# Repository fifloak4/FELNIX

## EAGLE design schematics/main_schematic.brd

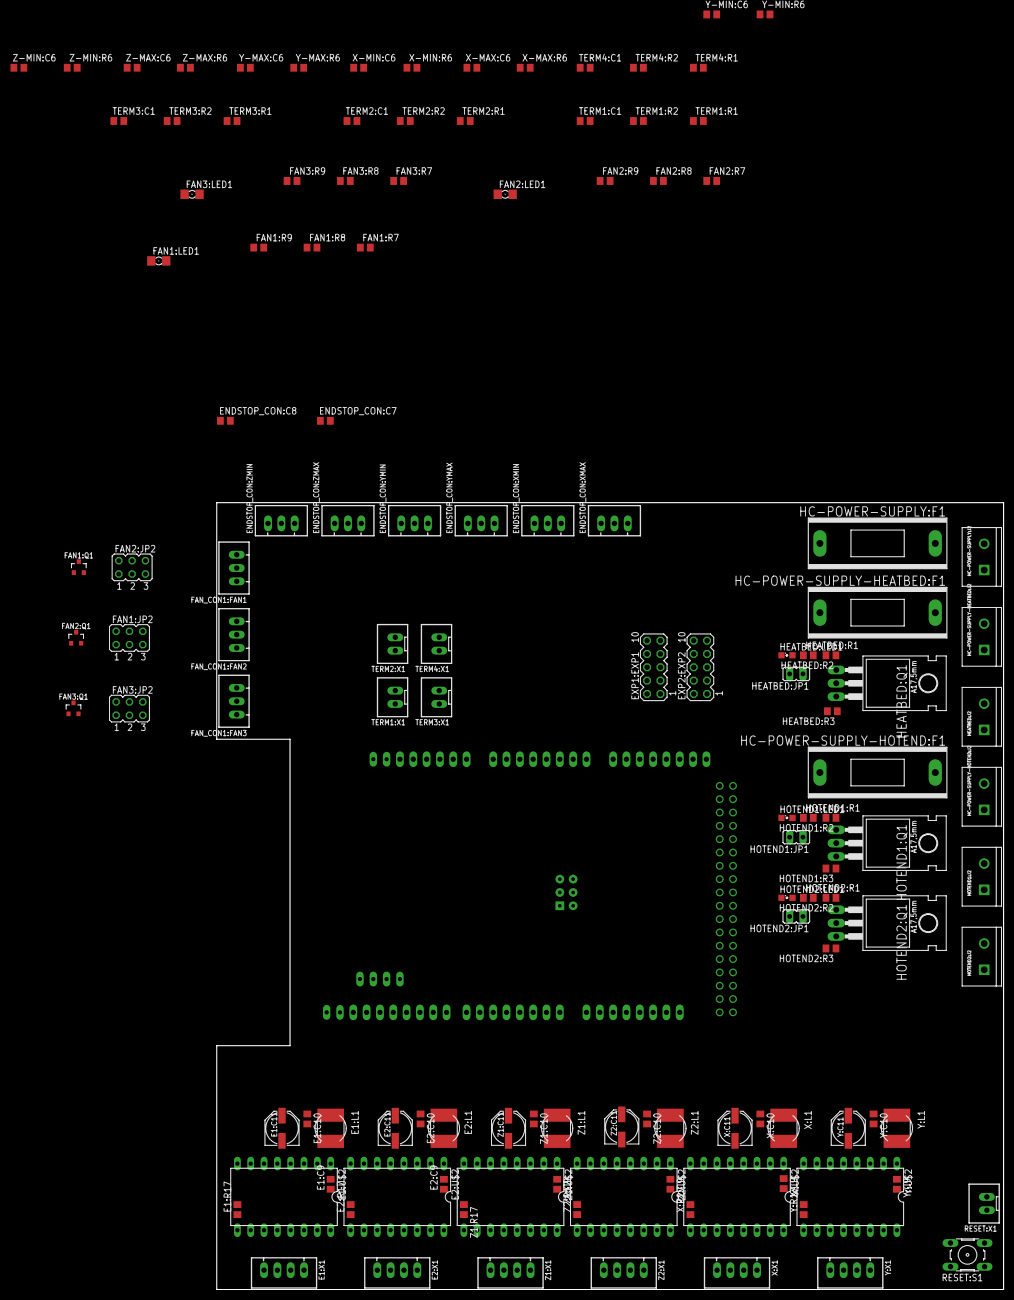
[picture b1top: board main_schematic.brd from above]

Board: 2 copper layers, 150.0 x 150.0 mm, 131 parts (1 on the bottom side), 126 nets, no tracks yet.

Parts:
ARDUINO_DUE:U$1: DUE(NORMAL)
E1:C9, E1:C10, E2:C9, E2:C10: 100nF 50V; C0805
E1:C11, E2:C11: 100uF 35V; PANASONIC_D
E1:L1, E2:L1: HPI0630-8R2; DLG-0504
E1:R17, E2:R17: 100k; R0805
E1:U$2, E2:U$2: POLOLUESTEPPERDRIVER; DIL16
E1:X1, E2:X1: MOTOR-OUT; JST-XH-04-PACKAGE-LONG-PAD
ENDSTOP_CON:C7, ENDSTOP_CON:C8: C0805
ENDSTOP_CON:XMAX: X-MAX; JST-XH-03-PACKAGE-LONG-PAD
ENDSTOP_CON:XMIN: X-MIN; JST-XH-03-PACKAGE-LONG-PAD
ENDSTOP_CON:YMAX: Y-MAX; JST-XH-03-PACKAGE-LONG-PAD
ENDSTOP_CON:YMIN: Y-MIN; JST-XH-03-PACKAGE-LONG-PAD
ENDSTOP_CON:ZMAX: Z-MAX; JST-XH-03-PACKAGE-LONG-PAD
ENDSTOP_CON:ZMIN: Z-MIN; JST-XH-03-PACKAGE-LONG-PAD
EXP1:EXP1, EXP2:EXP2: MA05-2
FAN1:JP2, FAN2:JP2, FAN3:JP2: FAN1_Vcc; JP3Q
FAN1:LED1, FAN2:LED1, FAN3:LED1: 1206
FAN1:Q1, FAN2:Q1, FAN3:Q1: IRLML0030TRPBF; SOT23-3
FAN1:R7, FAN2:R7, FAN3:R7: 2K7; R0805
FAN1:R8, FAN2:R8, FAN3:R8: 100R; R0805
FAN1:R9, FAN2:R9, FAN3:R9: 10K; R0805
FAN_CON1:FAN1: FAN1; JST-XH-03-PACKAGE-LONG-PAD
FAN_CON1:FAN2: FAN2; JST-XH-03-PACKAGE-LONG-PAD
FAN_CON1:FAN3: FAN3; JST-XH-03-PACKAGE-LONG-PAD
HC-POWER-SUPPLY-HEATBED:F1: SH22
HC-POWER-SUPPLY-HEATBED:J2: SCREWTERMINAL-5MM-2
HC-POWER-SUPPLY-HOTEND:F1: SH22
HC-POWER-SUPPLY-HOTEND:J2: SCREWTERMINAL-5MM-2
HC-POWER-SUPPLY:F1: SH22
HC-POWER-SUPPLY:J2: SCREWTERMINAL-5MM-2
HEATBED:J2: SCREWTERMINAL-5MM-2
HEATBED:JP1: JP1
HEATBED:LED1: SML0805
HEATBED:Q1: IRLRB8743; TO220AH
HEATBED:R1: 470R; R0805
HEATBED:R2: 100R; R0805
HEATBED:R3: 10K; R0805
HOTEND1:J2, HOTEND2:J2: SCREWTERMINAL-5MM-2
HOTEND1:JP1, HOTEND2:JP1: JP1
HOTEND1:LED1, HOTEND2:LED1: SML0805
HOTEND1:Q1, HOTEND2:Q1: IRLRB8743; TO220AH
HOTEND1:R1, HOTEND2:R1: 470R; R0805
HOTEND1:R2, HOTEND2:R2: 100R; R0805
HOTEND1:R3, HOTEND2:R3: 10K; R0805
RESET:S1: RESET; B3F-10XX
RESET:X1: RESET; JST-XH-02-PACKAGE-LONG-PAD
TERM1:C1, TERM2:C1, TERM3:C1, TERM4:C1: 10uF; C0805
TERM1:R1, TERM2:R1, TERM3:R1, TERM4:R1: 100R; R0805
TERM1:R2, TERM2:R2, TERM3:R2, TERM4:R2: 4K7; R0805
TERM1:X1, TERM2:X1, TERM3:X1, TERM4:X1: TERM; JST-XH-02-PACKAGE-LONG-PAD
X-MAX:C6: 100nF; C0805
X-MAX:R6: 10K; R0805
X-MIN:C6: 100nF; C0805
X-MIN:R6: 10K; R0805
X:C9, X:C10: 100nF 50V; C0805
X:C11: 100uF 35V; PANASONIC_D
X:L1: HPI0630-8R2; DLG-0504
X:R17: 100k; R0805
X:U$2: POLOLUESTEPPERDRIVER; DIL16
X:X1: MOTOR-OUT; JST-XH-04-PACKAGE-LONG-PAD
Y-MAX:C6: 100nF; C0805
Y-MAX:R6: 10K; R0805
Y-MIN:C6: 100nF; C0805
Y-MIN:R6: 10K; R0805
Y:C9, Y:C10: 100nF 50V; C0805
Y:C11: 100uF 35V; PANASONIC_D
Y:L1: HPI0630-8R2; DLG-0504
Y:R17: 100k; R0805
Y:U$2: POLOLUESTEPPERDRIVER; DIL16
Y:X1: MOTOR-OUT; JST-XH-04-PACKAGE-LONG-PAD
Z1:C9, Z1:C10, Z2:C9, Z2:C10: 100nF 50V; C0805
Z1:C11, Z2:C11: 100uF 35V; PANASONIC_D
Z1:L1, Z2:L1: HPI0630-8R2; DLG-0504
Z1:R17, Z2:R17: 100k; R0805
Z1:U$2, Z2:U$2: POLOLUESTEPPERDRIVER; DIL16
Z1:X1, Z2:X1: MOTOR-OUT; JST-XH-04-PACKAGE-LONG-PAD
Z-MAX:C6: 100nF; C0805
Z-MAX:R6: 10K; R0805
Z-MIN:C6: 100nF; C0805
Z-MIN:R6: 10K; R0805

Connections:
+3V3: ARDUINO_DUE:U$1.3V3, ARDUINO_DUE:U$1.IOREF, E1:R17.2, E1:U$2.7, E2:R17.2, E2:U$2.7, TERM1:R2.2, TERM2:R2.2, TERM3:R2.2, TERM4:R2.2, X:R17.2, X:U$2.7, Y:R17.2, Y:U$2.7, Z1:R17.2, Z1:U$2.7, Z2:R17.2, Z2:U$2.7
+5V: ARDUINO_DUE:U$1.5V, ARDUINO_DUE:U$1.GND_ICSP, ENDSTOP_CON:C7.1, ENDSTOP_CON:C8.1, ENDSTOP_CON:XMAX.2, ENDSTOP_CON:XMIN.2, ENDSTOP_CON:YMAX.2, ENDSTOP_CON:YMIN.2, ENDSTOP_CON:ZMAX.2, ENDSTOP_CON:ZMIN.2, EXP2:EXP2.9, FAN1:JP2.5, FAN2:JP2.5, FAN3:JP2.5
+12V: ARDUINO_DUE:U$1.VIN, FAN1:JP2.3, FAN2:JP2.3, FAN3:JP2.3
+24V: E1:C10.1, E1:C11.+, E1:L1.1, E2:C10.1, E2:C11.+, E2:L1.1, FAN1:JP2.1, FAN2:JP2.1, FAN3:JP2.1, HC-POWER-SUPPLY:F1.2, X:C10.1, X:C11.+, X:L1.1, Y:C10.1, Y:C11.+, Y:L1.1, Z1:C10.1, Z1:C11.+, Z1:L1.1, Z2:C10.1, Z2:C11.+, Z2:L1.1
E1:N$7: E1:U$2.3, E1:X1.4
E1:N$8: E1:U$2.4, E1:X1.3
E1:N$9: E1:U$2.5, E1:X1.2
E1:N$10: E1:U$2.6, E1:X1.1
E1:N$25: E1:C9.1, E1:L1.2, E1:U$2.1
E2:N$7: E2:U$2.3, E2:X1.4
E2:N$8: E2:U$2.4, E2:X1.3
E2:N$9: E2:U$2.5, E2:X1.2
E2:N$10: E2:U$2.6, E2:X1.1
E2:N$25: E2:C9.1, E2:L1.2, E2:U$2.1
FAN1:N$2: FAN1:LED1.A, FAN1:R7.2
FAN1:N$5: FAN1:Q1.1, FAN1:R8.2, FAN1:R9.1
FAN2:N$2: FAN2:LED1.A, FAN2:R7.2
FAN2:N$5: FAN2:Q1.1, FAN2:R8.2, FAN2:R9.1
FAN3:N$2: FAN3:LED1.A, FAN3:R7.2
FAN3:N$5: FAN3:Q1.1, FAN3:R8.2, FAN3:R9.1
GND: ARDUINO_DUE:U$1.5V_ICSP, ARDUINO_DUE:U$1.GND_1, ARDUINO_DUE:U$1.GND_2, E1:C9.2, E1:C10.2, E1:C11.-, E1:U$2.2, E1:U$2.8, E2:C9.2, E2:C10.2, E2:C11.-, E2:U$2.2, E2:U$2.8, ENDSTOP_CON:C7.2, ENDSTOP_CON:C8.2, ENDSTOP_CON:XMAX.1, ENDSTOP_CON:XMIN.1, ENDSTOP_CON:YMAX.1, ENDSTOP_CON:YMIN.1, ENDSTOP_CON:ZMAX.1, ENDSTOP_CON:ZMIN.1, EXP1:EXP1.10, EXP2:EXP2.10, FAN1:Q1.2, FAN1:R9.2, FAN2:Q1.2, FAN2:R9.2, FAN3:Q1.2, FAN3:R9.2, HC-POWER-SUPPLY:J2.1, HEATBED:LED1.C, HOTEND1:LED1.C, HOTEND2:LED1.C, RESET:S1.2, RESET:X1.1, TERM1:C1.1, TERM1:X1.2, TERM2:C1.1, TERM2:X1.2, TERM3:C1.1, TERM3:X1.2, TERM4:C1.1, TERM4:X1.2, X-MAX:C6.2, X-MIN:C6.2, X:C9.2, X:C10.2, X:C11.-, X:U$2.2, X:U$2.8, Y-MAX:C6.2, Y-MIN:C6.2, Y:C9.2, Y:C10.2, Y:C11.-, Y:U$2.2, Y:U$2.8, Z1:C9.2, Z1:C10.2, Z1:C11.-, Z1:U$2.2, Z1:U$2.8, Z2:C9.2, Z2:C10.2, Z2:C11.-, Z2:U$2.2, Z2:U$2.8, Z-MAX:C6.2, Z-MIN:C6.2
HC-POWER-SUPPLY-HEATBED:N$1: HC-POWER-SUPPLY-HEATBED:F1.1, HC-POWER-SUPPLY-HEATBED:J2.2
HC-POWER-SUPPLY-HOTEND:N$1: HC-POWER-SUPPLY-HOTEND:F1.1, HC-POWER-SUPPLY-HOTEND:J2.2
HC-POWER-SUPPLY:N$1: HC-POWER-SUPPLY:F1.1, HC-POWER-SUPPLY:J2.2
HEATBED:N$1: HEATBED:JP1.1, HEATBED:R1.2, HEATBED:R2.2
HEATBED:N$2: HEATBED:LED1.A, HEATBED:R1.1
HEATBED:N$3: HEATBED:Q1.B, HEATBED:R2.1, HEATBED:R3.2
HEATBED:N$4: HEATBED:J2.1, HEATBED:Q1.C
HOTEND1:N$1: HOTEND1:JP1.1, HOTEND1:R1.2, HOTEND1:R2.2
HOTEND1:N$2: HOTEND1:LED1.A, HOTEND1:R1.1
HOTEND1:N$3: HOTEND1:Q1.B, HOTEND1:R2.1, HOTEND1:R3.2
HOTEND1:N$4: HOTEND1:J2.1, HOTEND1:Q1.C
HOTEND2:N$1: HOTEND2:JP1.1, HOTEND2:R1.2, HOTEND2:R2.2
HOTEND2:N$2: HOTEND2:LED1.A, HOTEND2:R1.1
HOTEND2:N$3: HOTEND2:Q1.B, HOTEND2:R2.1, HOTEND2:R3.2
HOTEND2:N$4: HOTEND2:J2.1, HOTEND2:Q1.C
unnamed: ARDUINO_DUE:U$1.MISO_ICSP, E1:U$2.12, E2:U$2.12, EXP1:EXP1.2, X:U$2.12, Y:U$2.12, Z1:U$2.12, Z2:U$2.12
unnamed: ARDUINO_DUE:U$1.MOSI_ICSP, E1:U$2.15, E2:U$2.15, EXP1:EXP1.5, X:U$2.15, Y:U$2.15, Z1:U$2.15, Z2:U$2.15
unnamed: ARDUINO_DUE:U$1.SCK_ICSP, E1:U$2.14, E2:U$2.14, EXP1:EXP1.1, X:U$2.14, Y:U$2.14, Z1:U$2.14, Z2:U$2.14
unnamed: ARDUINO_DUE:U$1.RESET_ICSP, EXP1:EXP1.7, RESET:S1.4, RESET:X1.2
unnamed: ARDUINO_DUE:U$1.50, EXP1:EXP1.6
unnamed: ARDUINO_DUE:U$1.52, EXP1:EXP1.4
unnamed: ARDUINO_DUE:U$1.4, EXP1:EXP1.3
unnamed: ARDUINO_DUE:U$1.TX3, EXP1:EXP1.8
unnamed: ARDUINO_DUE:U$1.41, EXP2:EXP2.2
unnamed: ARDUINO_DUE:U$1.48, EXP2:EXP2.1
unnamed: ARDUINO_DUE:U$1.38, X-MIN:C6.1, X-MIN:R6.2
unnamed: ARDUINO_DUE:U$1.44, EXP2:EXP2.6
unnamed: ARDUINO_DUE:U$1.45, EXP2:EXP2.5
unnamed: ARDUINO_DUE:U$1.46, EXP2:EXP2.8
unnamed: ARDUINO_DUE:U$1.47, EXP2:EXP2.7
unnamed: ARDUINO_DUE:U$1.43, EXP2:EXP2.4
unnamed: ARDUINO_DUE:U$1.42, EXP2:EXP2.3
unnamed: ARDUINO_DUE:U$1.22, X:R17.1, X:U$2.16
unnamed: ARDUINO_DUE:U$1.2, X:U$2.10
unnamed: ARDUINO_DUE:U$1.3, X:U$2.9
unnamed: ARDUINO_DUE:U$1.26, Y:R17.1, Y:U$2.16
unnamed: ARDUINO_DUE:U$1.RX2, Y:U$2.10
unnamed: ARDUINO_DUE:U$1.TX2, Y:U$2.9
unnamed: ARDUINO_DUE:U$1.36, X-MAX:C6.1, X-MAX:R6.2
unnamed: ARDUINO_DUE:U$1.RX3, Z1:R17.1, Z1:U$2.16
unnamed: ARDUINO_DUE:U$1.34, Y-MIN:C6.1, Y-MIN:R6.2
unnamed: ARDUINO_DUE:U$1.32, Y-MAX:C6.1, Y-MAX:R6.2
unnamed: ARDUINO_DUE:U$1.30, Z-MIN:C6.1, Z-MIN:R6.2
unnamed: ARDUINO_DUE:U$1.28, Z-MAX:C6.1, Z-MAX:R6.2
unnamed: ENDSTOP_CON:XMAX.3, X-MIN:R6.1
unnamed: ENDSTOP_CON:XMIN.3, X-MAX:R6.1
unnamed: ENDSTOP_CON:YMAX.3, Y-MIN:R6.1
unnamed: ENDSTOP_CON:YMIN.3, Y-MAX:R6.1
unnamed: ENDSTOP_CON:ZMAX.3, Z-MIN:R6.1
unnamed: ENDSTOP_CON:ZMIN.3, Z-MAX:R6.1
unnamed: FAN1:JP2.2, FAN1:JP2.4, FAN1:JP2.6, FAN1:R7.1, FAN_CON1:FAN1.2
unnamed: FAN1:LED1.C, FAN1:Q1.3, FAN_CON1:FAN1.3
unnamed: FAN2:JP2.2, FAN2:JP2.4, FAN2:JP2.6, FAN2:R7.1, FAN_CON1:FAN2.2
unnamed: FAN2:LED1.C, FAN2:Q1.3, FAN_CON1:FAN2.3
unnamed: FAN3:JP2.2, FAN3:JP2.4, FAN3:JP2.6, FAN3:R7.1, FAN_CON1:FAN3.2
unnamed: FAN3:LED1.C, FAN3:Q1.3, FAN_CON1:FAN3.3
unnamed: ARDUINO_DUE:U$1.A7, Z1:U$2.10
unnamed: ARDUINO_DUE:U$1.A6, Z1:U$2.9
unnamed: ARDUINO_DUE:U$1.A8, Z2:R17.1, Z2:U$2.16
unnamed: ARDUINO_DUE:U$1.A10, Z2:U$2.10
unnamed: ARDUINO_DUE:U$1.A9, Z2:U$2.9
unnamed: ARDUINO_DUE:U$1.A11, E1:R17.1, E1:U$2.16
unnamed: ARDUINO_DUE:U$1.11, FAN1:R8.1
unnamed: ARDUINO_DUE:U$1.9, FAN2:R8.1
unnamed: ARDUINO_DUE:U$1.12, FAN3:R8.1
unnamed: ARDUINO_DUE:U$1.51, E1:U$2.10
unnamed: ARDUINO_DUE:U$1.53, E1:U$2.9
unnamed: ARDUINO_DUE:U$1.49, E2:R17.1, E2:U$2.16
unnamed: ARDUINO_DUE:U$1.24, E2:U$2.10
unnamed: ARDUINO_DUE:U$1.23, E2:U$2.9
unnamed: HC-POWER-SUPPLY-HOTEND:J2.1, HOTEND1:Q1.E, HOTEND1:R3.1, HOTEND2:Q1.E, HOTEND2:R3.1
unnamed: HC-POWER-SUPPLY-HOTEND:F1.2, HOTEND1:J2.2, HOTEND2:J2.2
unnamed: ARDUINO_DUE:U$1.7, HOTEND2:JP1.2
unnamed: ARDUINO_DUE:U$1.8, HOTEND1:JP1.2
unnamed: HC-POWER-SUPPLY-HEATBED:J2.1, HEATBED:Q1.E, HEATBED:R3.1
unnamed: HC-POWER-SUPPLY-HEATBED:F1.2, HEATBED:J2.2
unnamed: ARDUINO_DUE:U$1.39, HEATBED:JP1.2
unnamed: ARDUINO_DUE:U$1.A5, TERM4:R1.1
unnamed: ARDUINO_DUE:U$1.A2, TERM3:R1.1
unnamed: ARDUINO_DUE:U$1.A1, TERM2:R1.1
unnamed: ARDUINO_DUE:U$1.A0, TERM1:R1.1
TERM1:N$1: TERM1:C1.2, TERM1:R1.2, TERM1:R2.1, TERM1:X1.1
TERM2:N$1: TERM2:C1.2, TERM2:R1.2, TERM2:R2.1, TERM2:X1.1
TERM3:N$1: TERM3:C1.2, TERM3:R1.2, TERM3:R2.1, TERM3:X1.1
TERM4:N$1: TERM4:C1.2, TERM4:R1.2, TERM4:R2.1, TERM4:X1.1
X:N$7: X:U$2.3, X:X1.4
X:N$8: X:U$2.4, X:X1.3
X:N$9: X:U$2.5, X:X1.2
X:N$10: X:U$2.6, X:X1.1
X:N$25: X:C9.1, X:L1.2, X:U$2.1
Y:N$7: Y:U$2.3, Y:X1.4
Y:N$8: Y:U$2.4, Y:X1.3
Y:N$9: Y:U$2.5, Y:X1.2
Y:N$10: Y:U$2.6, Y:X1.1
Y:N$25: Y:C9.1, Y:L1.2, Y:U$2.1
Z1:N$7: Z1:U$2.3, Z1:X1.4
Z1:N$8: Z1:U$2.4, Z1:X1.3
Z1:N$9: Z1:U$2.5, Z1:X1.2
Z1:N$10: Z1:U$2.6, Z1:X1.1
Z1:N$25: Z1:C9.1, Z1:L1.2, Z1:U$2.1
Z2:N$7: Z2:U$2.3, Z2:X1.4
Z2:N$8: Z2:U$2.4, Z2:X1.3
Z2:N$9: Z2:U$2.5, Z2:X1.2
Z2:N$10: Z2:U$2.6, Z2:X1.1
Z2:N$25: Z2:C9.1, Z2:L1.2, Z2:U$2.1

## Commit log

2018-03-10 Schematic created
    simple due shield added
2018-03-10 Arduino DUE Labeled compatibile with Due3Dom
2018-03-10 Endstops added
2018-03-10 Fans sheet created
2018-03-10 Fan connectors added
2018-03-10 Fan jumpers fixed
2018-03-12 Schematic converted to hierarchical layout
2018-03-12 EXP1 and EXP2 added
2018-03-13 Motors modules added
2018-03-13 Reset module added
2018-03-14 *.brd created, minor changes in schematic
2018-03-15 Working on PCB

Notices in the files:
parts and their libraries:
SparkFun-Connectors: Licensing: Creative Commons ShareAlike 4.0 International - https://creativecommons.org/licenses/by-sa/4.0
